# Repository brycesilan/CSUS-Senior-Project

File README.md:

# CSUS Senior Project

Vertical farming applies modern technologies to revolutionize the traditional agriculture process that has remained unchanged for millennia. Because traditional farming is limited in a 2D space it is very efficient at utilizing a given amount of land for food production. Transitioning the possible area, we can cultivate to a 3D space that can sustain exponentially larger yields than a traditional farm. Vertical farming uses a soilless method of growing food, meaning we can grow the food anywhere in the world with higher yields and fewer resources. With the human population on Earth exploding, the only way we can support the food demands of the future is to expand our food production capabilities into a whole new dimension… Up

A Collaboration with Silicon Valley Mechatronics

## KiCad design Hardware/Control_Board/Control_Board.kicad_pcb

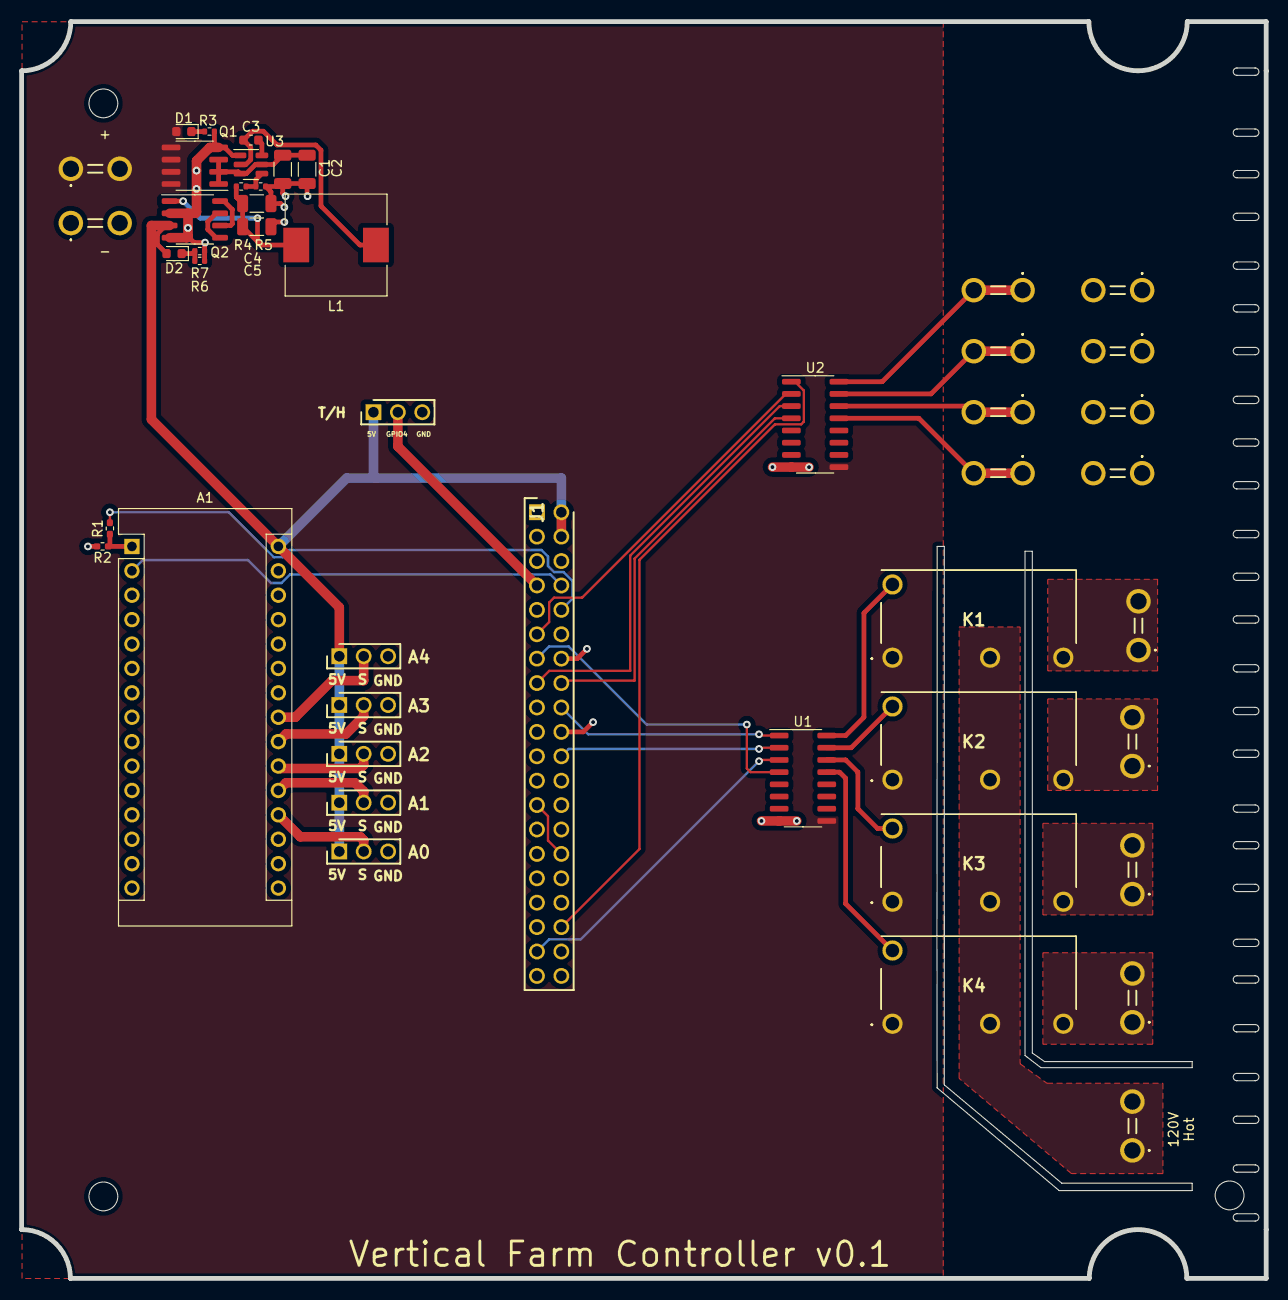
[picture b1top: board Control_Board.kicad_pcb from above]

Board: 2 copper layers, 129.5 x 130.8 mm, 47 parts (0 on the bottom side), 41 nets.

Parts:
A0, A2, A3, A4: HDRV3W64P0X254_1X3_762X254X864P
A1: Arduino_Nano_v3.x; Arduino_Nano
A1#2: Arduino_Nano_v3.x; HDRV3W64P0X254_1X3_762X254X864P
C1, C2: 10uF; C_1206_3216Metric
C3: 100nF; C_0603_1608Metric
C4, C5: 22uF; C_1206_3216Metric
D1, D2: LED_Red_power; LED_0603_1608Metric
J1: Raspberry_Pi_2_3; HDRV40W64P254_2X20_5080X500X884P
J2, J3: Screw_Terminal_01x02; 197054301
J4, J5, J6, J8, J112: 19705-4301; 197054301
J**: 197054301
J**#2, J**#3, J**#4, J**#5, J**#6, J**#7, J**#8: 197054301
K1, K2, K3, K4: ALQ3F12; G5Q1A4DC24
L1: 3.3uH; L_10.4x10.4_H4.8
Q1: PMOS; SOIC-8_3.9x4.9mm_P1.27mm
Q2: Q_Dual_PMOS_S1G1S2G2D2D2D1D1; SOP-8_3.9x4.9mm_P1.27mm
R1: 10k; R_0402_1005Metric_Pad0.72x0.64mm_HandSolder
R2: 20k; R_0402_1005Metric_Pad0.72x0.64mm_HandSolder
R3, R5: 10k; R_0402_1005Metric
R4: 56.2k; R_0402_1005Metric
R6, R7: 6.8k; R_0402_1005Metric
T/H: HDRV3W64P0X254_1X3_762X254X864P
U1, U2: ULN2003; SOIC-16_3.9x9.9mm_P1.27mm
U3: TPS563200; SOT-23-6

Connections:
120V_Hot: J8.1, J8.2, K1.2 (NO), K2.2 (NO), K3.2 (NO), K4.2 (NO)
+5V: A0.1, A1.30 (VIN), A1#2.1 (D1/TX), A2.1, A3.1, A4.1, D2.2 (A), J1.2 (5V), J1.4 (5V), Q2.3 (S), T/H.1
+12V: D1.2 (A), J2.1, J2.2, K1.1 (Coil), K2.1 (Coil), K3.1 (Coil), K4.1 (Coil), Q1.5, Q1.6, Q1.7, Q1.8, U1.9 (COM), U2.9 (COM)
A0: A0.2, A1.19 (A0)
A1: A1.20 (A1), A1#2.2 (D0/RX)
A2: A1.21 (A2), A2.2
A3: A1.22 (A3), A3.2
A4: A1.23 (A4), A4.2
GND: A0.3, A1.4 (GND), A1.29 (GND), A1#2.3 (~RESET), A2.3, A3.3, A4.3, C1.2, C2.2, C4.2, C5.2, J1.6 (GND), J1.9 (GND), J1.14 (GND), J1.20 (GND), J1.25 (GND), J1.30 (GND), J1.34 (GND), J1.39 (GND), J3.1, J3.2, J**#2.1, J**#2.2, J**#4.1, J**#4.2, J**#5.1, J**#5.2, J**#7.1, J**#7.2, Q1.4, Q2.2 (G), Q2.4 (G), R2.2, R3.1, R5.1, R6.1, R7.1, T/H.3, U1.8 (GND), U2.8 (GND), U3.1 (GND)
unnamed: C1.1, C2.1, Q1.1 (D), Q1.2 (G), Q1.3 (eS), U3.3 (VIN), U3.5 (EN)
unnamed: C3.1, L1.1, U3.2 (SW)
unnamed: C3.2, U3.6 (VBST)
unnamed: C4.1, C5.1, L1.2, Q2.1 (S), R4.2
unnamed: D1.1 (K), R3.2
unnamed: D2.1 (K), R6.2, R7.2
unnamed: J1.10 (GPIO15/RXD), R1.1
unnamed: J4.1, J4.2, K1.3 (COM)
unnamed: J5.1, J5.2, K2.3 (COM)
unnamed: J6.1, J6.2, K3.3 (COM)
unnamed: J112.1, J112.2, K4.3 (COM)
unnamed: Q2.5 (D), Q2.7 (D)
unnamed: Q2.6 (G), Q2.8 (G)
unnamed: R4.1, R5.2, U3.4 (VFB)
Pump1: J**#3.1, J**#3.2, U2.16 (O1)
Pump2: J**#6.1, J**#6.2, U2.15 (O2)
Pump3: J**.1, J**.2, U2.14 (O3)
Pump4: J**#8.1, J**#8.2, U2.13 (O4)
RX: A1.1 (D1/TX), R1.2, R2.1
Relay1: K1.5 (Coil), U1.16 (O1)
Relay2: K2.5 (Coil), U1.15 (O2)
Relay3: K3.5 (Coil), U1.14 (O3)
Relay4: K4.5 (Coil), U1.13 (O4)
TX: A1.2 (D0/RX), J1.8 (GPIO14/TXD)
U1/Pin1: J1.18 (GPIO24), U1.1 (I1)
U1/Pin2: J1.22 (GPIO25), U1.2 (I2)
U1/Pin3: J1.37 (GPIO26), U1.3 (I3)
U1/Pin4: J1.13 (GPIO27), U1.4 (I4)
U2/Pin1: J1.36 (GPIO16), U2.1 (I1)
U2/Pin2: J1.11 (GPIO17), U2.2 (I2)
U2/Pin3: J1.15 (GPIO22), U2.3 (I3)
U2/Pin4: J1.16 (GPIO23), U2.4 (I4)

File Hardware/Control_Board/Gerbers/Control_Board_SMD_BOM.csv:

Comment,Designator,Footprint
3.3uH,L1,L_10.4x10.4_H4.8
10uF,"C2,C1",C_1206_3216Metric
6.8k,"R6,R7",R_0402_1005Metric
20k,R2,R_0402_1005Metric_Pad0.72x0.64mm_HandSolder
LED_Red_power,"D2,D1",LED_0603_1608Metric
22uF,"C5,C4",C_1206_3216Metric
Q_Dual_PMOS_S1G1S2G2D2D2D1D1,Q2,SOP-8_3.9x4.9mm_P1.27mm
56.2k,R4,R_0402_1005Metric
10k,"R5,R3",R_0402_1005Metric
TPS563200,U3,SOT-23-6
ULN2003,"U2,U1",SOIC-16_3.9x9.9mm_P1.27mm
10k,R1,R_0402_1005Metric_Pad0.72x0.64mm_HandSolder
PMOS,Q1,SOIC-8_3.9x4.9mm_P1.27mm
100nF,C3,C_0603_1608Metric

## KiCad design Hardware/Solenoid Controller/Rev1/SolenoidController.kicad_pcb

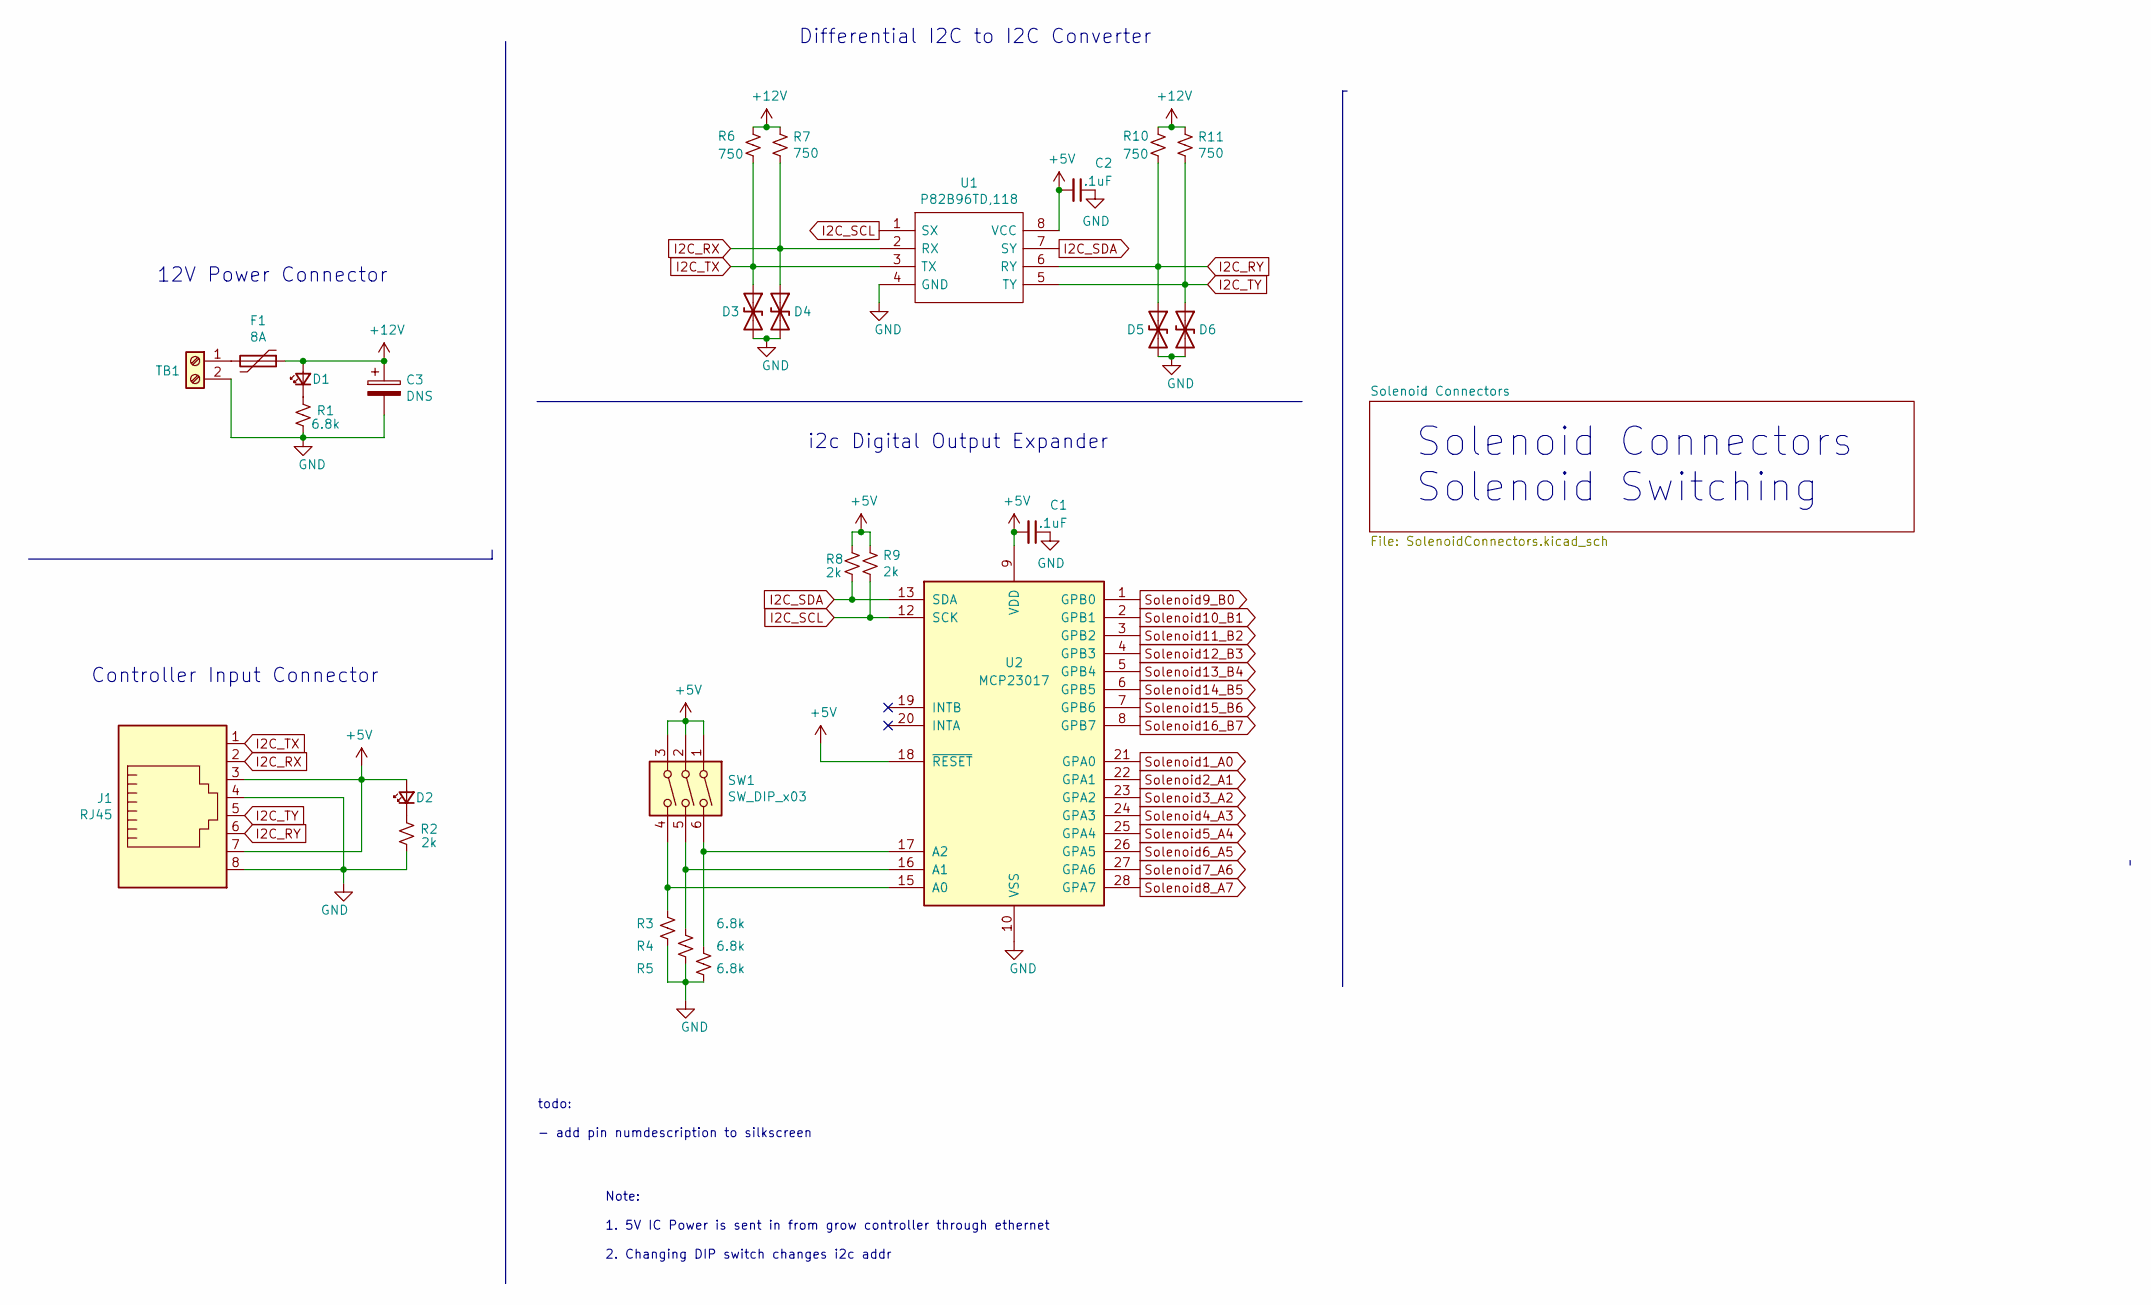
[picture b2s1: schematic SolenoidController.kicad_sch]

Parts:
C1, C2: .1uF; C_0402_1005Metric; MFG PN CL05B104KO5NNNC; LCSC PN C1525
C3: DNS; CP_Radial_D8.0mm_P3.50mm
D1, D2: LED_Red; LED_0603_1608Metric
D3, D4, D5, D6: D_TVS; D_SOD-123
F1: 8A; Fuse_2920_7451Metric
J1: RJ45; RJ45_Ninigi_GE
R1, R3, R4, R5: 6.8k; R_0402_1005Metric
R2, R8, R9: 2k; R_0402_1005Metric
R6, R7, R10, R11: 750; R_1206_3216Metric
SW1: SW_DIP_x03; SW_DIP_SPSTx03_Slide_9.78x9.8mm_W7.62mm_P2.54mm
TB1: Screw_Terminal_01x02; KF250-3.5-2P-1
U1: P82B96TD,118; Manufacturer_Part_Number P82B96TD,118; Mouser Part Number 771-P82B96TD-T
U2: MCP23017; SOIC-28W_7.5x17.9mm_P1.27mm; MFG PN MCP23017; LCSC PN C47023

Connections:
+5V: C1.2, C2.2, D2.2 (A), J1.3, J1.7, R8.1, R9.1, SW1.1, SW1.2, SW1.3, U1.8 (VCC), U2.9 (VDD), U2.18 (~RESET)
+12V: C3.1, D1.2 (A), F1.1, R6.1, R7.1, R10.1, R11.1; also elsewhere on the board
GND: C1.1, C2.1, C3.2, D3.2 (A2), D4.2 (A2), D5.2 (A2), D6.2 (A2), J1.4, J1.8, J1.SH, R1.1, R2.1, R3.2, R4.2, R5.2, TB1.2, U1.4 (GND), U2.10 (VSS); also elsewhere on the board
I2C_RX: D4.1 (A1), J1.2, R7.2, U1.2 (RX)
I2C_RY: D5.1 (A1), J1.6, R10.2, U1.6 (RY)
I2C_SCL: R9.2, U1.1 (SX), U2.12 (SCK)
I2C_SDA: R8.2, U1.7 (SY), U2.13 (SDA)
I2C_TX: D3.1 (A1), J1.1, R6.2, U1.3 (TX)
I2C_TY: D6.1 (A1), J1.5, R11.2, U1.5 (TY)
unnamed: D1.1 (K), R1.2
unnamed: D2.1 (K), R2.2
unnamed: F1.2, TB1.1
unnamed: R3.1, SW1.4, U2.15 (A0)
unnamed: R4.1, SW1.5, U2.16 (A1)
unnamed: R5.1, SW1.6, U2.17 (A2)
Solenoid1_A0: U2.21 (GPA0); also elsewhere on the board
Solenoid2_A1: U2.22 (GPA1); also elsewhere on the board
Solenoid3_A2: U2.23 (GPA2); also elsewhere on the board
Solenoid4_A3: U2.24 (GPA3); also elsewhere on the board
Solenoid5_A4: U2.25 (GPA4); also elsewhere on the board
Solenoid6_A5: U2.26 (GPA5); also elsewhere on the board
Solenoid7_A6: U2.27 (GPA6); also elsewhere on the board
Solenoid8_A7: U2.28 (GPA7); also elsewhere on the board
Solenoid9_B0: U2.1 (GPB0); also elsewhere on the board
Solenoid10_B1: U2.2 (GPB1); also elsewhere on the board
Solenoid11_B2: U2.3 (GPB2); also elsewhere on the board
Solenoid12_B3: U2.4 (GPB3); also elsewhere on the board
Solenoid13_B4: U2.5 (GPB4); also elsewhere on the board
Solenoid14_B5: U2.6 (GPB5); also elsewhere on the board
Solenoid15_B6: U2.7 (GPB6); also elsewhere on the board
Solenoid16_B7: U2.8 (GPB7); also elsewhere on the board

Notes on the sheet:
Differential I2C to I2C Converter
Note: 1. 5V IC Power is sent in from grow controller through ethernet 2. Changing DIP switch changes i2c addr
12V Power Connector
Controller Input Connector
todo: - add pin numdescription to silkscreen
Solenoid Connectors Solenoid Switching
i2c Digital Output Expander

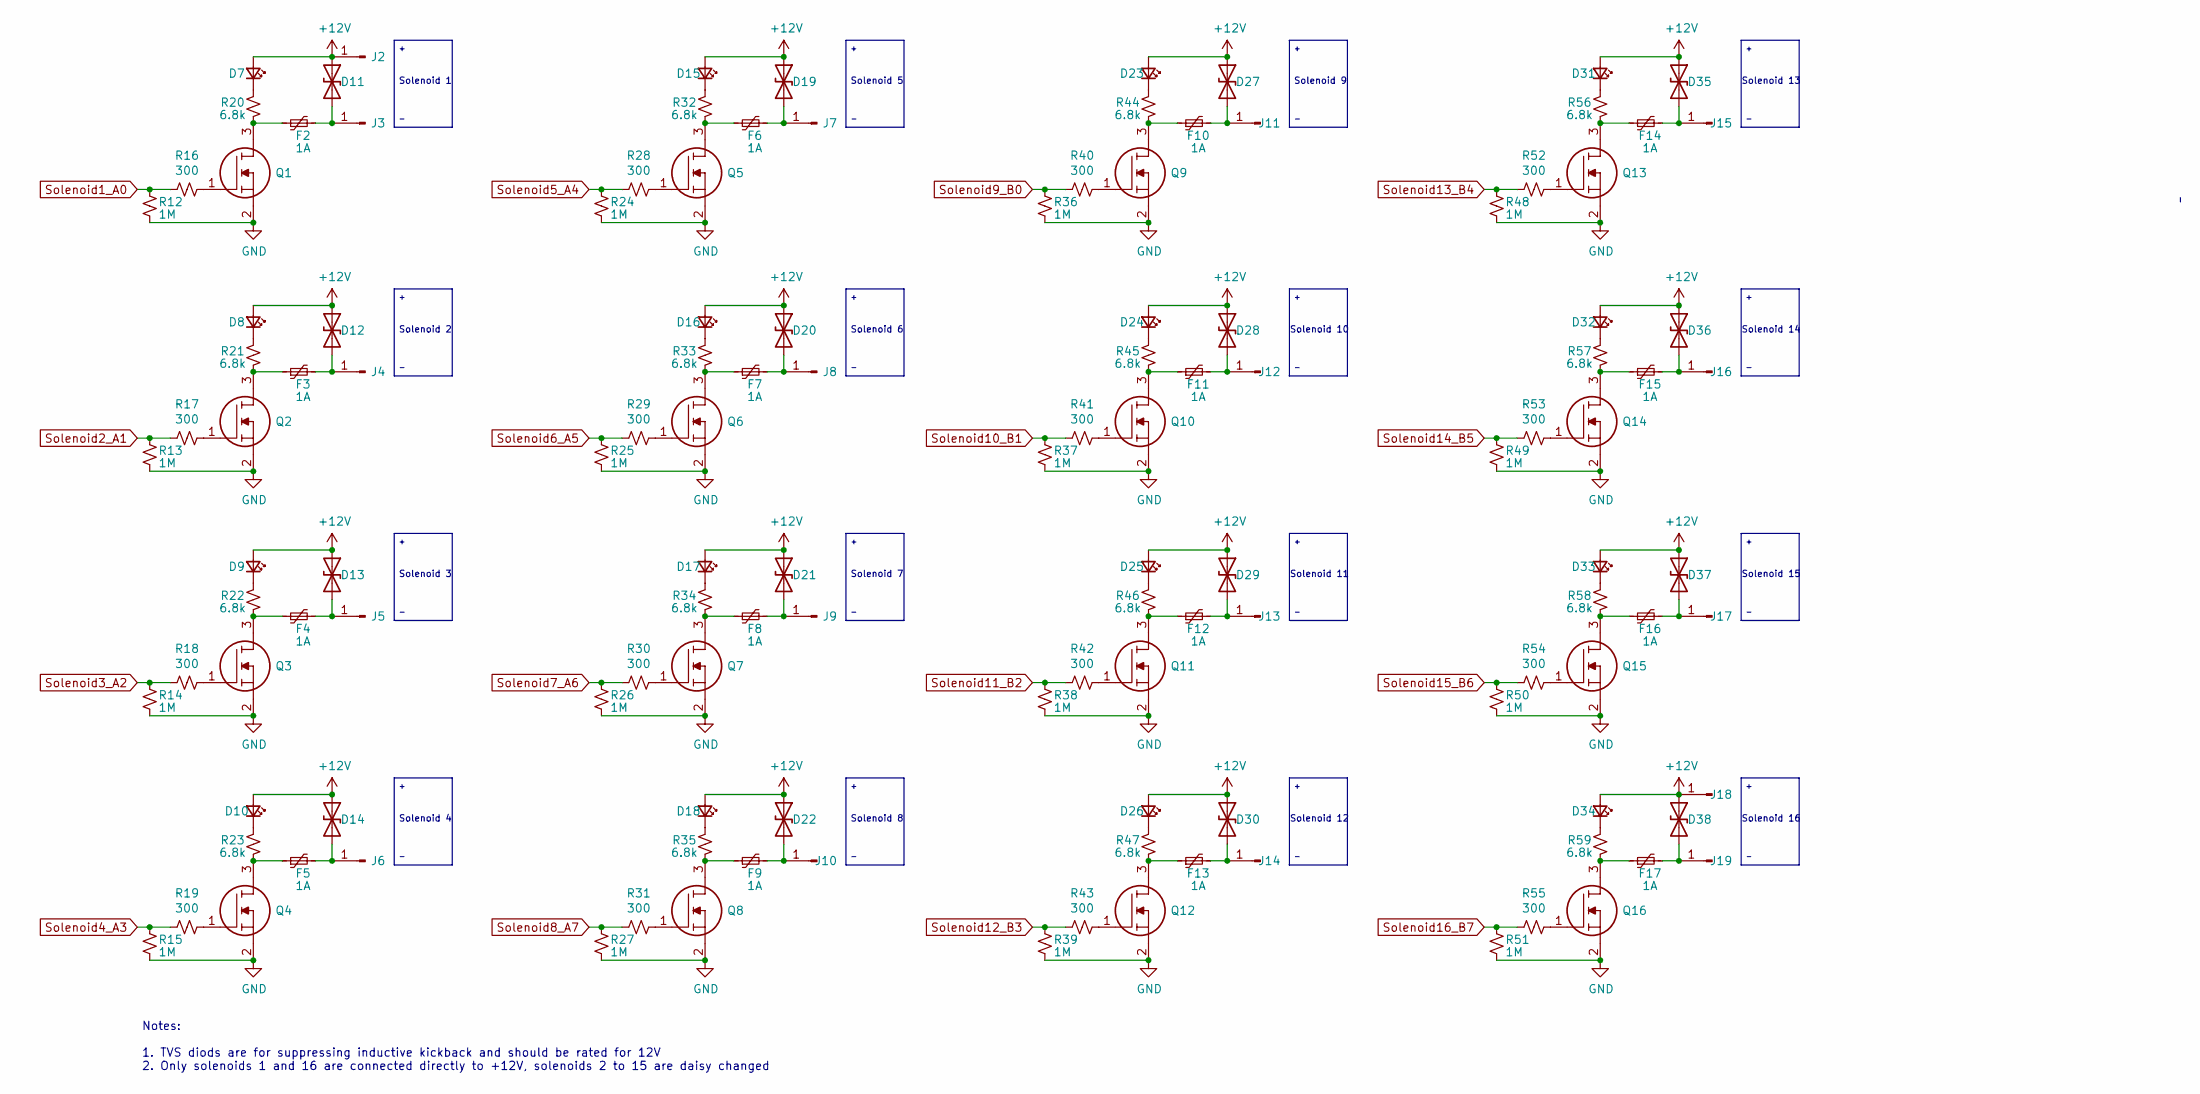
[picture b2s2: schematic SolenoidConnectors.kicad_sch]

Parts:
D7, D8, D9, D10, D15, D16, D17, D18, D23, D24, D25, D26, D31, D32, D33, D34: LED_Green; LED_0603_1608Metric
D11, D12, D13, D14, D19, D20, D21, D22, D27, D28, D29, D30, D35, D36, D37, D38: D_TVS; D_SOD-123
F2, F3, F4, F5, F6, F7, F8, F9, F10, F11, F12, F13, F14, F15, F16, F17: 1A; Fuse_1206_3216Metric
J2, J3, J4, J5, J6, J7, J8, J9, J10, J11, J12, J13, J14, J15, J16, J17, J18, J19: Conn_01x01_Male; 1287
Q1, Q2, Q3, Q4, Q5, Q6, Q7, Q8, Q9, Q10, Q11, Q12, Q13, Q14, Q15, Q16: AO3400A; SOT-23; Manufacturer_Part_Number SI2312CDS-T1-GE3; Mouser Part Number 781-SI2312CDS-T1-GE3
R12, R13, R14, R15, R24, R25, R26, R27, R36, R37, R38, R39, R48, R49, R50, R51: 1M; R_0402_1005Metric
R16, R17, R18, R19, R28, R29, R30, R31, R40, R41, R42, R43, R52, R53, R54, R55: 300; R_0402_1005Metric
R20, R21, R22, R23, R32, R33, R34, R35, R44, R45, R46, R47, R56, R57, R58, R59: 6.8k; R_0402_1005Metric

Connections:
+12V: D7.2 (A), D8.2 (A), D9.2 (A), D10.2 (A), D11.1 (A1), D12.1 (A1), D13.1 (A1), D14.1 (A1), D15.2 (A), D16.2 (A), D17.2 (A), D18.2 (A), D19.1 (A1), D20.1 (A1), D21.1 (A1), D22.1 (A1), D23.2 (A), D24.2 (A), D25.2 (A), D26.2 (A), D27.1 (A1), D28.1 (A1), D29.1 (A1), D30.1 (A1), D31.2 (A), D32.2 (A), D33.2 (A), D34.2 (A), D35.1 (A1), D36.1 (A1), D37.1 (A1), D38.1 (A1), J2.1, J18.1; also elsewhere on the board
GND: Q1.2, Q2.2, Q3.2, Q4.2, Q5.2, Q6.2, Q7.2, Q8.2, Q9.2, Q10.2, Q11.2, Q12.2, Q13.2, Q14.2, Q15.2, Q16.2, R12.2, R13.2, R14.2, R15.2, R24.2, R25.2, R26.2, R27.2, R36.2, R37.2, R38.2, R39.2, R48.2, R49.2, R50.2, R51.2; also elsewhere on the board
unnamed: D7.1 (K), R20.2
unnamed: D8.1 (K), R21.2
unnamed: D9.1 (K), R22.2
unnamed: D10.1 (K), R23.2
unnamed: D11.2 (A2), F2.2, J3.1
unnamed: D12.2 (A2), F3.2, J4.1
unnamed: D13.2 (A2), F4.2, J5.1
unnamed: D14.2 (A2), F5.2, J6.1
unnamed: D15.1 (K), R32.2
unnamed: D16.1 (K), R33.2
unnamed: D17.1 (K), R34.2
unnamed: D18.1 (K), R35.2
unnamed: D19.2 (A2), F6.2, J7.1
unnamed: D20.2 (A2), F7.2, J8.1
unnamed: D21.2 (A2), F8.2, J9.1
unnamed: D22.2 (A2), F9.2, J10.1
unnamed: D23.1 (K), R44.2
unnamed: D24.1 (K), R45.2
unnamed: D25.1 (K), R46.2
unnamed: D26.1 (K), R47.2
unnamed: D27.2 (A2), F10.2, J11.1
unnamed: D28.2 (A2), F11.2, J12.1
unnamed: D29.2 (A2), F12.2, J13.1
unnamed: D30.2 (A2), F13.2, J14.1
unnamed: D31.1 (K), R56.2
unnamed: D32.1 (K), R57.2
unnamed: D33.1 (K), R58.2
unnamed: D34.1 (K), R59.2
unnamed: D35.2 (A2), F14.2, J15.1
unnamed: D36.2 (A2), F15.2, J16.1
unnamed: D37.2 (A2), F16.2, J17.1
unnamed: D38.2 (A2), F17.2, J19.1
unnamed: F2.1, Q1.3, R20.1
unnamed: F3.1, Q2.3, R21.1
unnamed: F4.1, Q3.3, R22.1
unnamed: F5.1, Q4.3, R23.1
unnamed: F6.1, Q5.3, R32.1
unnamed: F7.1, Q6.3, R33.1
unnamed: F8.1, Q7.3, R34.1
unnamed: F9.1, Q8.3, R35.1
unnamed: F10.1, Q9.3, R44.1
unnamed: F11.1, Q10.3, R45.1
unnamed: F12.1, Q11.3, R46.1
unnamed: F13.1, Q12.3, R47.1
unnamed: F14.1, Q13.3, R56.1
unnamed: F15.1, Q14.3, R57.1
unnamed: F16.1, Q15.3, R58.1
unnamed: F17.1, Q16.3, R59.1
unnamed: Q1.1, R16.1
unnamed: Q2.1, R17.1
unnamed: Q3.1, R18.1
unnamed: Q4.1, R19.1
unnamed: Q5.1, R28.1
unnamed: Q6.1, R29.1
unnamed: Q7.1, R30.1
unnamed: Q8.1, R31.1
unnamed: Q9.1, R40.1
unnamed: Q10.1, R41.1
unnamed: Q11.1, R42.1
unnamed: Q12.1, R43.1
unnamed: Q13.1, R52.1
unnamed: Q14.1, R53.1
unnamed: Q15.1, R54.1
unnamed: Q16.1, R55.1
Solenoid1_A0: R12.1, R16.2; also elsewhere on the board
Solenoid2_A1: R13.1, R17.2; also elsewhere on the board
Solenoid3_A2: R14.1, R18.2; also elsewhere on the board
Solenoid4_A3: R15.1, R19.2; also elsewhere on the board
Solenoid5_A4: R24.1, R28.2; also elsewhere on the board
Solenoid6_A5: R25.1, R29.2; also elsewhere on the board
Solenoid7_A6: R26.1, R30.2; also elsewhere on the board
Solenoid8_A7: R27.1, R31.2; also elsewhere on the board
Solenoid9_B0: R36.1, R40.2; also elsewhere on the board
Solenoid10_B1: R37.1, R41.2; also elsewhere on the board
Solenoid11_B2: R38.1, R42.2; also elsewhere on the board
Solenoid12_B3: R39.1, R43.2; also elsewhere on the board
Solenoid13_B4: R48.1, R52.2; also elsewhere on the board
Solenoid14_B5: R49.1, R53.2; also elsewhere on the board
Solenoid15_B6: R50.1, R54.2; also elsewhere on the board
Solenoid16_B7: R51.1, R55.2; also elsewhere on the board

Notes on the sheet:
Solenoid 13
Notes: 1. TVS diods are for suppressing inductive kickback and should be rated for 12V 2. Only solenoids 1 and 16 are connected directly to +12V, solenoids 2 to 15 are daisy changed
Solenoid 14
Solenoid 8
Solenoid 11
Solenoid 6
Solenoid 5
Solenoid 2
Solenoid 9
Solenoid 12
Solenoid 1
Solenoid 16
Solenoid 15
Solenoid 10
Solenoid 7
Solenoid 4
Solenoid 3

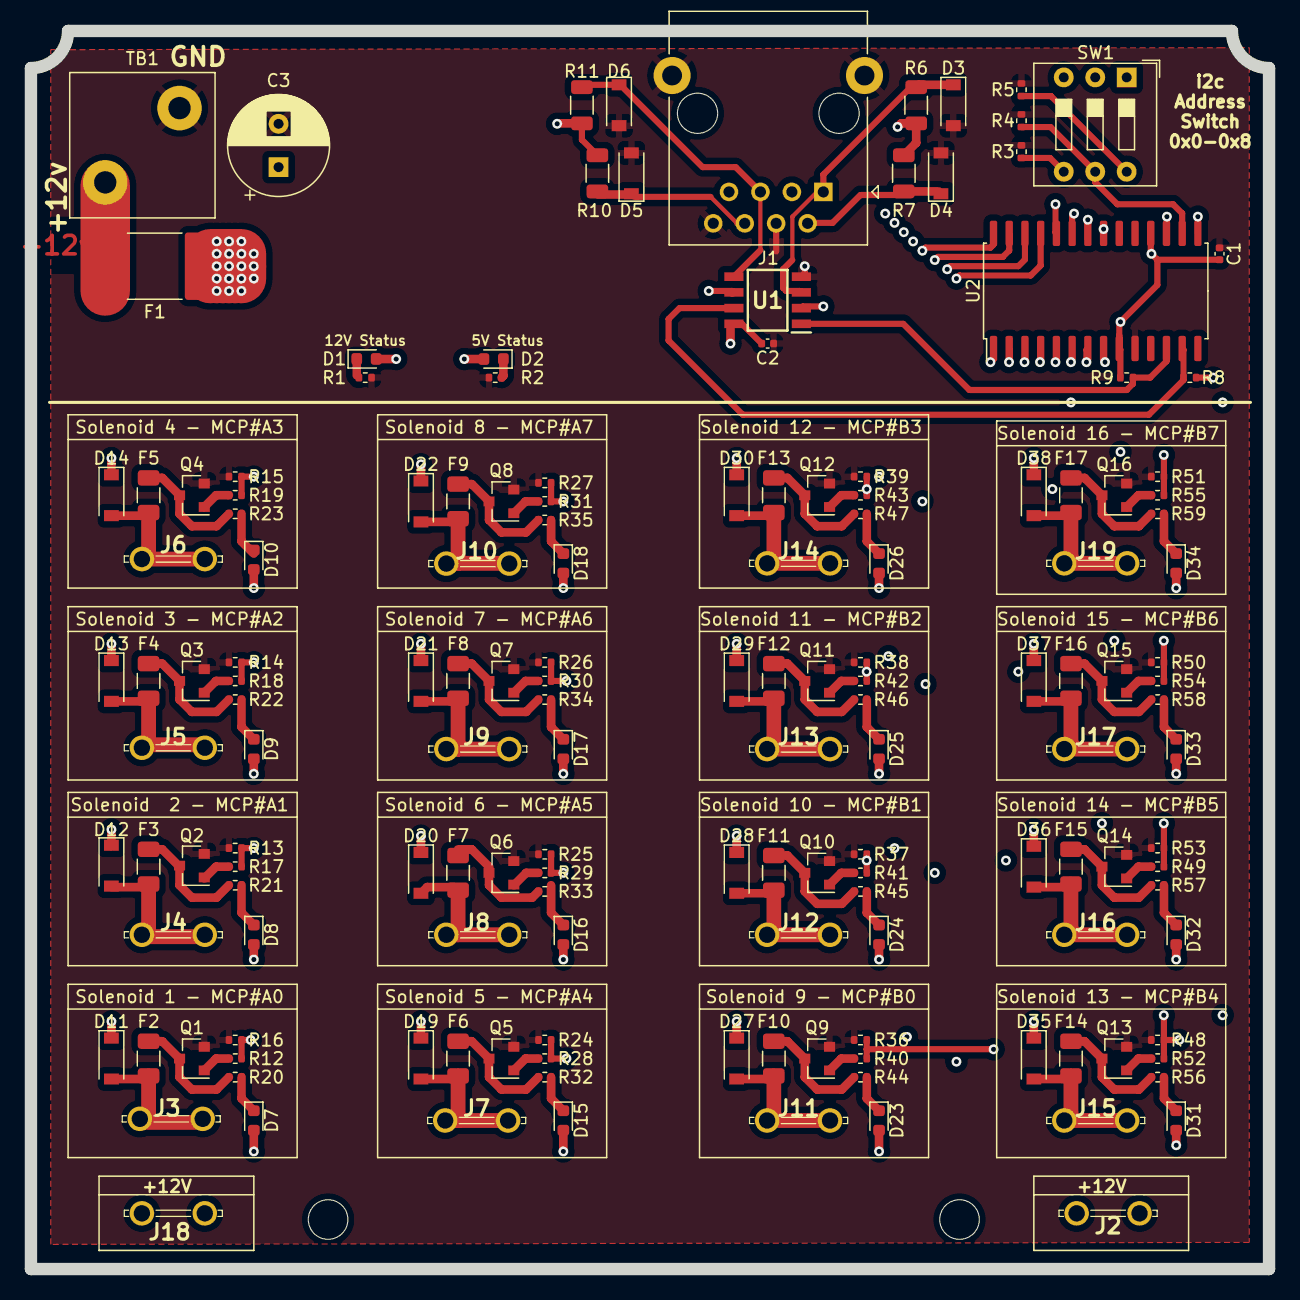
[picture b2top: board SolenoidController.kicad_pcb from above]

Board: 4 copper layers, 100.0 x 100.0 mm, 156 parts (0 on the bottom side), 95 nets.

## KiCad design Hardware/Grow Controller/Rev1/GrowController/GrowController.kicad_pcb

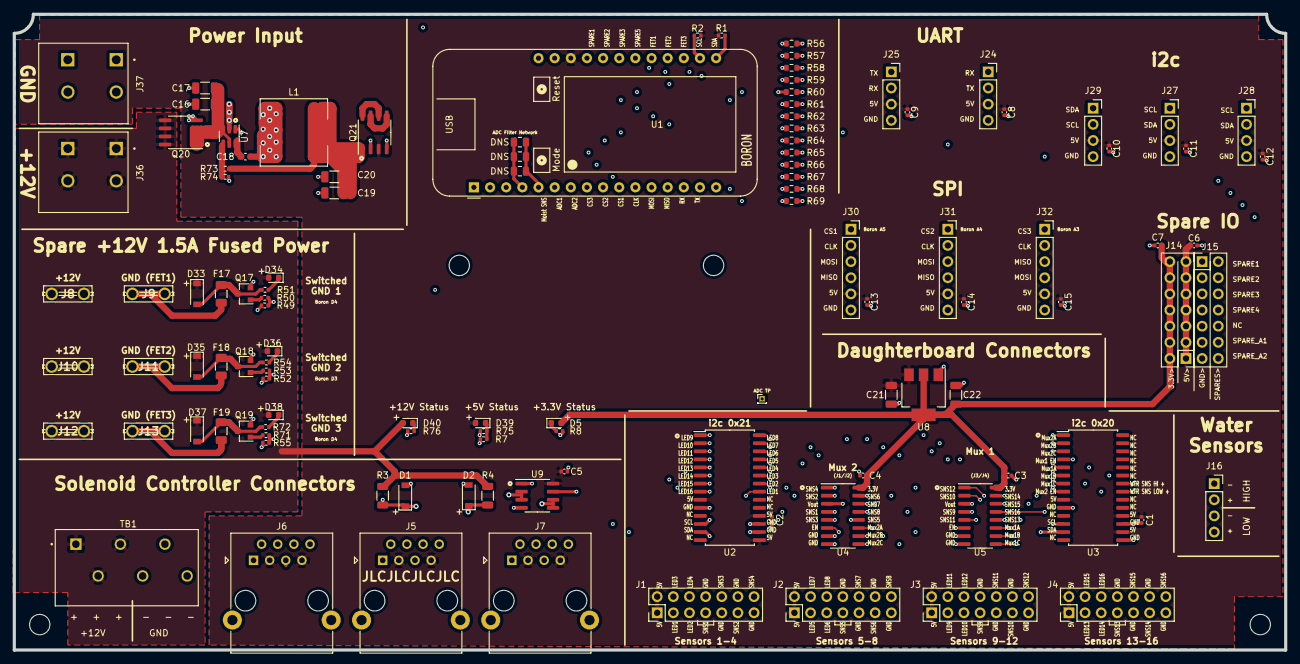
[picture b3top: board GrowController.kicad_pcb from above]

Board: 4 copper layers, 200.0 x 100.0 mm, 113 parts (0 on the bottom side), 104 nets.

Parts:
C1, C2, C3, C4, C5, C6, C7, C8, C9, C10, C11, C12, C13, C14, C15: .1uF; C_0402_1005Metric
C16, C17, C21: 10uF; C_1206_3216Metric
C18: 100nF; C_0603_1608Metric
C19, C20, C22: 22uF; C_1206_3216Metric
D1, D2, D33, D35, D37: SMF12A; D_SOD-123
D5, D39, D40: LED_Red_power; LED_0603_1608Metric
D34, D36, D38: LED_Green_indicator; LED_0603_1608Metric
DNS: C_0805_2012Metric
DNS#2, DNS#3: C_0805_2012Metric
F17, F18, F19: 1A; Fuse_1206_3216Metric
J1, J2, J3, J4, J14, J15: Conn_02x07_Odd_Even; PinHeader_2x07_P2.54mm_Vertical
J5, J6, J7: RJ45; RJ45_Ninigi_GE
J8, J9, J10, J11, J12, J13: Conn_01x01_Male; 1287
J16, J24, J25, J27, J28, J29: Header_01x04_Female; PinSocket_1x04_P2.54mm_Vertical
J30, J31, J32: Header_01x06_Female; PinSocket_1x06_P2.54mm_Vertical
J36, J37: Screw_Terminal_01x02; CUI_TBL004-508-02BE-2GY
L1: 3.3uH; L_10.4x10.4_H4.8
Q17, Q18, Q19: SI2312CDS-T1-GE3; SOT-23
Q20: PMOS; SOIC-8_3.9x4.9mm_P1.27mm
Q21: Q_Dual_PMOS_S1G1S2G2D2D2D1D1; SOP-8_3.9x4.9mm_P1.27mm
R1, R2: 2k; R_0402_1005Metric
R3, R4: 750; R_1206_3216Metric
R7, R8, R51, R54, R72, R75: 6.8k; R_0402_1005Metric
R49, R52, R55: 1M; R_0402_1005Metric
R50, R53, R71: 300; R_0402_1005Metric
R56, R57, R58, R59, R60, R61, R62, R63, R64, R65, R66, R67, R68, R69: 100; R_0603_1608Metric
R73: 56.2k; R_0402_1005Metric
R74, R76: 10k; R_0402_1005Metric
TB1: Screw_Terminal_01x06; CUI_TBL002A-350-06GY-2GY
U1: Particle; Particle_Boron
U2, U3: MCP23017; SOIC-28W_7.5x17.9mm_P1.27mm
U4, U5: SN74LV4051ADR; SOIC-16_3.9x9.9mm_P1.27mm
U7: TPS563200; SOT-23-6
U8: AMS1117-3.3; SOT-223-3_TabPin2
U9: P82B96TD,118; SOIC-8_3.9x4.9mm_P1.27mm

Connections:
+3.3VA: C3.2, C4.2, C7.1, C22.1, D5.2, J14.2, J14.4, J14.6, J14.8, J14.10, J14.12, J14.14, U4.16, U5.16, U8.2
+5V: C1.2, C2.2, C5.2, C6.1, C8.1, C9.1, C10.1, C11.1, C12.1, C13.1, C14.1, C15.1, C21.1, D39.2, J1.1, J1.2, J2.1, J2.2, J3.1, J3.2, J4.1, J4.2, J5.3, J5.7, J6.3, J6.7, J7.3, J7.7, J14.1, J14.3, J14.5, J14.7, J14.9, J14.11, J14.13, J24.3, J25.3, J27.3, J28.3, J29.3, J30.5, J31.5, J32.5, Q21.3, R1.1, R2.1, U1.9, U2.9, U2.15, U2.18, U3.9, U3.16, U3.18, U8.3, U9.8
+12V: D33.1, D34.2, D35.1, D36.2, D37.1, D38.2, D40.2, J8.1, J10.1, J12.1, J36.1, J36.2, Q20.5, Q20.6, Q20.7, Q20.8, R3.1, R4.1, TB1.1, TB1.2, TB1.3
CLK_ESD: J30.2, J31.2, J32.2, R60.1
CS1_ESD: J30.1, R63.1
CS2_ESD: J31.1, R64.1
CS3_ESD: J32.1, R65.1
GND: C1.1, C2.1, C3.1, C4.1, C5.1, C6.2, C7.2, C8.2, C9.2, C10.2, C11.2, C12.2, C13.2, C14.2, C15.2, C16.2, C17.2, C19.2, C20.2, C21.2, C22.2, D1.2, D2.2, DNS.1, DNS#2.1, DNS#3.1, J1.8, J1.9, J1.12, J1.13, J2.8, J2.9, J2.12, J2.13, J3.8, J3.9, J3.12, J3.13, J4.8, J4.9, J4.12, J4.13, J5.4, J5.8, J6.4, J6.8, J7.4, J7.8, J15.1, J15.3, J15.5, J15.7, J15.9, J15.11, J15.13, J16.1, J16.3, J24.4, J25.4, J27.4, J28.4, J29.4, J30.6, J31.6, J32.6, J37.1, J37.2, Q17.2, Q18.2, Q19.2, Q20.4, Q21.2, Q21.4, R7.1, R8.1, R49.2, R52.2, R55.2, R74.1, R75.1, R76.1, TB1.4, TB1.5, TB1.6, U1.24, U2.10, U2.16, U2.17, U3.10, U3.15, U3.17, U4.7, U4.8, U5.7, U5.8, U7.1, U8.1, U9.4
I2C_SCL: R2.2, R56.2, U1.1, U2.12, U3.12, U9.1
I2C_SDA: R1.2, R57.2, U1.0, U2.13, U3.13, U9.7
LED1_1xA0: J1.3, U2.21
LED2_1xA1: J1.5, U2.22
LED3_1xA2: J1.4, U2.23
LED4_1xA3: J1.6, U2.24
LED5_1xA4: J2.3, U2.25
LED6_1xA5: J2.5, U2.26
LED7_1xA6: J2.4, U2.27
LED8_1xA7: J2.6, U2.28
LED9_1xB0: J3.3, U2.1
LED10_1xB1: J3.5, U2.2
LED11_1xB2: J3.4, U2.3
LED12_1xB3: J3.6, U2.4
LED13_1xB4: J4.3, U2.5
LED14_1xB5: J4.5, U2.6
LED15_1xB6: J4.4, U2.7
LED16_1xB7: J4.6, U2.8
MISO_ESD: J30.4, J31.4, J32.3, R62.1
MOSI_ESD: J30.3, J31.3, J32.4, R61.1
MoistureSensor_ADC: DNS.2, DNS#2.2, DNS#3.2, U1.23, U4.3, U5.3
Mux1A_2xB4: U3.5, U5.11
Mux1B_2xB5: U3.6, U5.10
Mux1C_2xB6: U3.7, U5.9
Mux1INH_2xB3: U3.4, U5.6
Mux2A_2xB0: U3.1, U4.11
Mux2B_2xB1: U3.2, U4.10
Mux2C_2xB2: U3.3, U4.9
Mux2INH_2xB7: U3.8, U4.6
unnamed: C16.1, C17.1, Q20.1, Q20.2, Q20.3, U7.3, U7.5
unnamed: C18.1, L1.1, U7.2
unnamed: C18.2, U7.6
unnamed: C19.1, C20.1, L1.2, Q21.1, R73.2
unnamed: D5.1, R8.2
unnamed: D33.2, F17.2, Q17.3, R51.1
unnamed: D34.1, R51.2
unnamed: D35.2, F18.2, Q18.3, R54.1
unnamed: D36.1, R54.2
unnamed: D37.2, F19.2, Q19.3, R72.1
unnamed: D38.1, R72.2
unnamed: D39.1, R7.2, R75.2
unnamed: D40.1, R76.2
unnamed: F17.1, J9.1
unnamed: F18.1, J11.1
unnamed: F19.1, J13.1
unnamed: Q17.1, R50.1
unnamed: Q18.1, R53.1
unnamed: Q19.1, R71.1
unnamed: Q21.5, Q21.7
unnamed: Q21.6, Q21.8
unnamed: R73.1, R74.2, U7.4
SCL_ESD: J27.1, J28.1, J29.2, R56.1
SDA_ESD: J27.2, J28.2, J29.1, R57.1
SENSOR1: J1.7, U4.4
SENSOR2: J1.11, U4.2
SENSOR3: J1.10, U4.5
SENSOR4: J1.14, U4.1
SENSOR5: J2.7, U4.12
SENSOR6: J2.11, U4.15
SENSOR7: J2.10, U4.14
SENSOR8: J2.14, U4.13
SENSOR9: J3.7, U5.4
SENSOR10: J3.11, U5.2
SENSOR11: J3.10, U5.5
SENSOR12: J3.14, U5.1
SENSOR13: J4.7, U5.12
SENSOR14: J4.11, U5.15
SENSOR15: J4.10, U5.14
SENSOR16: J4.14, U5.13
SPARE1: R66.2, U1.8
SPARE1_ESD: J15.2, R66.1
SPARE2: R67.2, U1.7
SPARE2_ESD: J15.4, R67.1
SPARE3: R68.2, U1.6
SPARE3_ESD: J15.6, R68.1
SPARE4: R69.2, U1.5
SPARE4_ESD: J15.8, R69.1
SPARE_ANALOG1: J15.12, U1.21
SPARE_ANALOG2: J15.14, U1.22
SPARE_FET1: R49.1, R50.2, U1.4
SPARE_FET2: R52.1, R53.2, U1.3
SPARE_FET3: R55.1, R71.2, U1.2
SPI_CLK: R60.2, U1.17
SPI_CS1: R63.2, U1.18
SPI_CS2: R64.2, U1.19
SPI_CS3: R65.2, U1.20
SPI_MISO: R62.2, U1.15
SPI_MOSI: R61.2, U1.16
UART_RX: R58.2, U1.14
UART_RX_ESD: J24.1, J25.2, R58.1
UART_TX: R59.2, U1.13
UART_TX_ESD: J24.2, J25.1, R59.1
WaterSensorHIGH_2xA1: J16.2, U3.22
WaterSensorLOW_2xA0: J16.4, U3.21
dI2C_SCL: D1.1, J5.1, J5.2, J6.1, J6.2, J7.1, J7.2, R3.2, U9.2, U9.3
dI2C_SDA: D2.1, J5.5, J5.6, J6.5, J6.6, J7.5, J7.6, R4.2, U9.5, U9.6

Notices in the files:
parts and their libraries:
Copyright 2016 Accelerated Designs. All rights reserved.
